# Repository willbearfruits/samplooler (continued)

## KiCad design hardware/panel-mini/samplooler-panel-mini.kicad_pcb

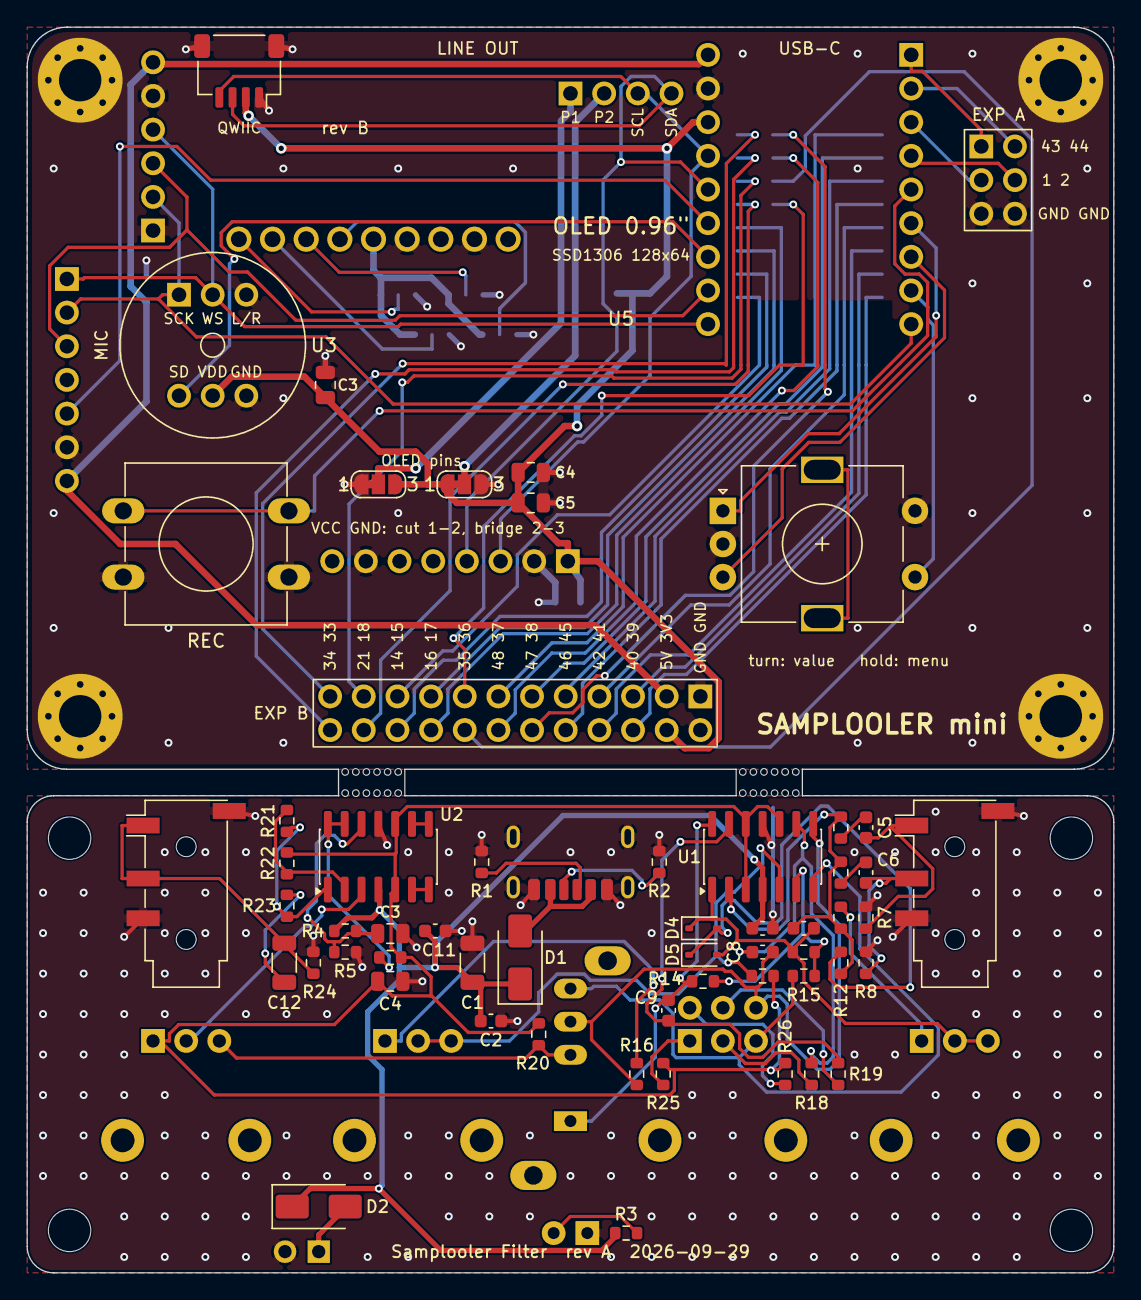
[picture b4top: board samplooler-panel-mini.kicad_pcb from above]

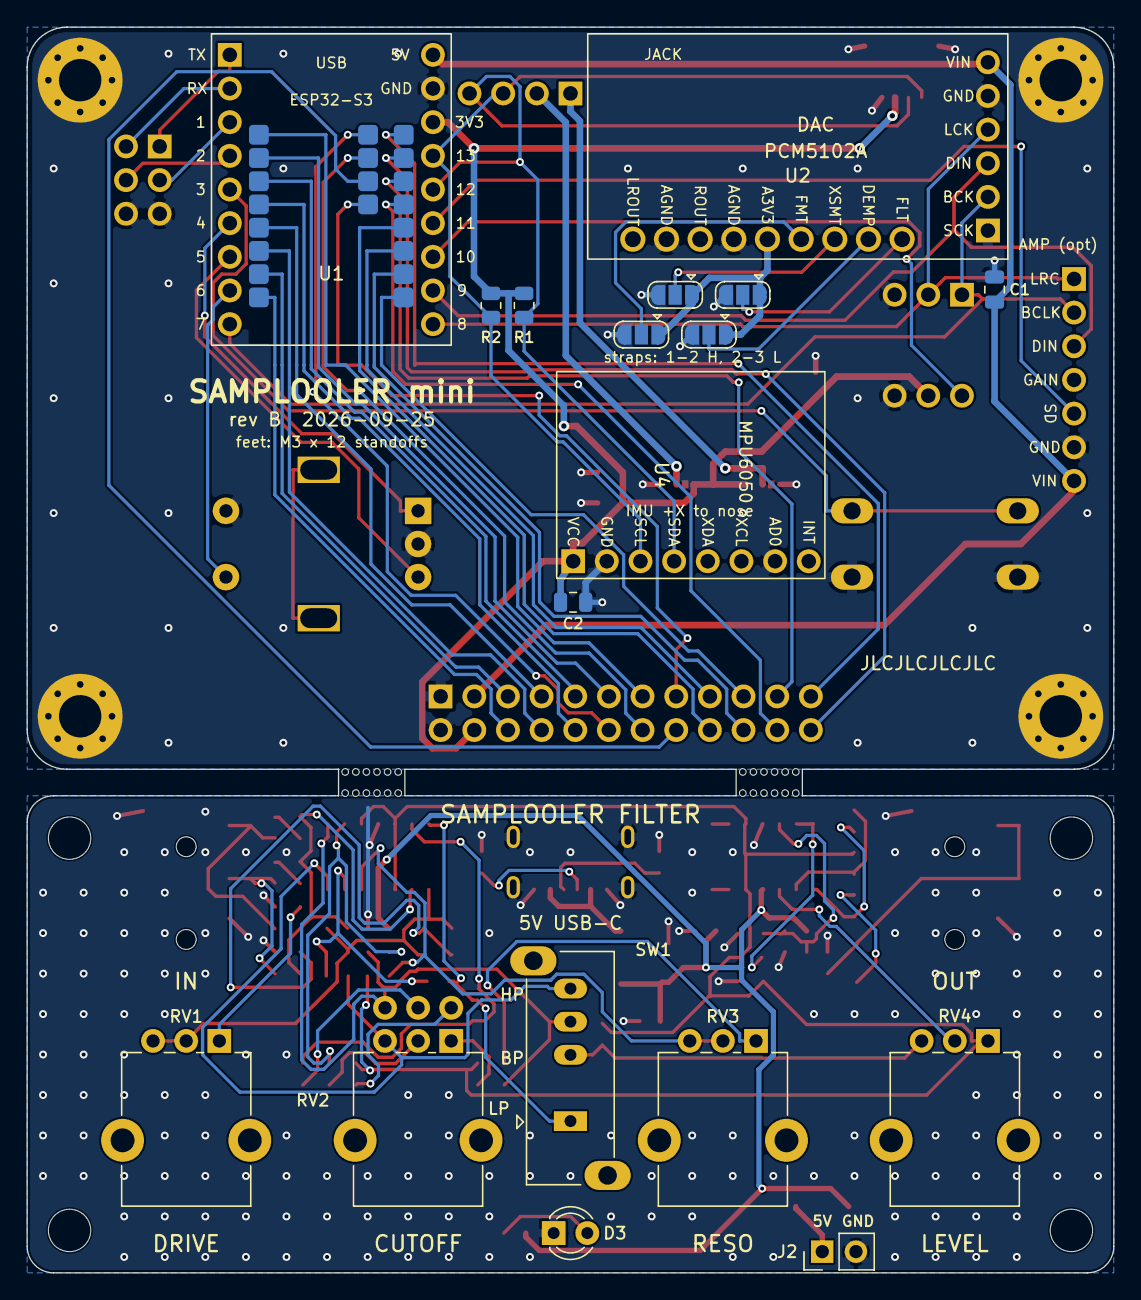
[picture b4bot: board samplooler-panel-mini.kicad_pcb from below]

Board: 2 copper layers, 82.0 x 94.0 mm, 86 parts (19 on the bottom side), 81 nets.

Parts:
C1, C12: 47u; C_1206_3216Metric
C1#2, C3, C4, C4#2: 10u; C_0805_2012Metric
C2, C10, C11: 100n; C_0603_1608Metric
C2#2, C3#2, C5#2: 100n; C_0805_2012Metric
C5, C6: 1u; C_0603_1608Metric
C7: 100p; C_0603_1608Metric
C8, C9: 3.3n; C_0603_1608Metric
D1, D2: SS14; D_SMA
D3: LED 3mm; LED_D3.0mm
D4, D5: 1N4148W; D_SOD-323
H1, H2, H3#2, H4: M3; MountingHole_3.2mm_M3_Pad_Via
H1#2, H2#2, H3, H4#2: M3; MountingHole_3.2mm_M3
J1: USB-C (power); USB_C_Receptacle_HRO_TYPE-C-31-M-17_NoSilkOverPegs
J2: 5V IN; PinHeader_1x02_P2.54mm_Vertical
J2#2: MAX98357A (opt); MAX98357A_Breakout
J3: IN; Jack_3.5mm_PJ320D_Horizontal
J3#2: Qwiic I2C; JST_SH_SM04B-SRSS-TB_1x04-1MP_P1.00mm_Horizontal
J4: OUT; Jack_3.5mm_PJ320D_Horizontal
J4#2: EXP A; EXP_A_2x3_Mini
J5: EXP B; EXP_B_2x12_Mini
JP1: FLT; SolderJumper-3_P1.3mm_Open_RoundedPad1.0x1.5mm
JP2: DEMP; SolderJumper-3_P1.3mm_Open_RoundedPad1.0x1.5mm
JP3: XSMT; SolderJumper-3_P1.3mm_Open_RoundedPad1.0x1.5mm
JP4: FMT; SolderJumper-3_P1.3mm_Open_RoundedPad1.0x1.5mm
JP5: OLED pin 1; SolderJumper-3_P1.3mm_Bridged12_RoundedPad1.0x1.5mm_NumberL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
JP6: OLED pin 2; SolderJumper-3_P1.3mm_Bridged12_RoundedPad1.0x1.5mm_NumberL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
R1, R2: 5k1; R_0603_1608Metric
R1#2, R2#2: 4k7; R_0805_2012Metric
R3, R11, R12: 2k2; R_0603_1608Metric
R4, R5, R14, R15, R22: 10k; R_0603_1608Metric
R6, R25, R26: 100R; R_0603_1608Metric
R7, R8, R20: 100k; R_0603_1608Metric
R9, R10, R21: 22k; R_0603_1608Metric
R13: 33k; R_0603_1608Metric
R16: 470R; R_0603_1608Metric
R17: 1k5; R_0603_1608Metric
R18, R19: 4k7; R_0603_1608Metric
R23: 47R; R_0603_1608Metric
R24: 47k; R_0603_1608Metric
RV1: B100K; Potentiometer_Alpha_RD901F-40-00D_Single_Vertical_CircularH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
RV2: A10K dual; Potentiometer_Alpha_RD902F-40-00D_Dual_Vertical_CircularHol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
RV3: A50K; Potentiometer_Alpha_RD901F-40-00D_Single_Vertical_CircularH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
RV4: A10K; Potentiometer_Alpha_RD901F-40-00D_Single_Vertical_CircularH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
SW1: EC11, 20 mm shaft; RotaryEncoder_Alps_EC11E-Switch_Vertical_H20mm
SW1#2: LP BP HP; SW_Slide_SP3T_Straight_CK_OS103012MU1QP1
SW2: 12 mm tactile + cap; SW_PUSH-12mm
U1, U2: MCP6004; SOIC-14_3.9x8.7mm_P1.27mm
U1#2: ESP32-S3_SuperMini
U2#2: PCM5102A; GY-PCM5102
U3: INMP441; INMP441_Round
U4: MPU6050; GY-521_MPU6050
U5: OLED 0.96in; SSD1306_0.96in_I2C_NoHoles

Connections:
+3V3: C2#2.1, C3#2.1, C4.1, C5#2.1, J3#2.2, J5.4 (3V3), JP5.3, JP6.1, R1#2.1, R2#2.1, U1#2.12 (3V3), U3.5 (VDD), U4.1 (VCC)
+5V: C1.1, C1#2.1, C2.1, C10.1, C11.1, D1.1, D2.1, J2#2.7 (VIN), J5.3 (5V), R3.1, R4.1, U1.4, U1#2.10 (5V), U2.4, U2#2.6 (VIN)
/5V_EXT: D2.2, J2.1
/AC_L: C5.2, R9.1
/AC_R: C6.2, R10.1
/AMP_SD: J2#2.5 (SD), U1#2.15 (11)
/BP: C8.2, R16.1, RV2.6, SW1#2.3, U1.8
/CC1: J1.A5, R1.1
/CC2: J1.B5, R2.1
/CF1: R25.1, RV2.1
/CF2: R26.1, RV2.4
/CLP: D4.2, D5.1, R12.2
/DAC_3V3: JP1.1, JP2.1, JP3.1, JP4.1, U2#2.11 (A3V3)
/DAC_DEMP: JP2.2, U2#2.8 (DEMP)
/DAC_FLT: JP1.2, U2#2.7 (FLT)
/DAC_FMT: JP4.2, U2#2.10 (FMT)
/DAC_XSMT: JP3.2, U2#2.9 (XSMT)
/DRV: C7.2, D4.1, D5.2, R13.1, RV1.2, RV1.3, U1.1
/DRV_N: C7.1, R9.2, R10.2, R11.1, R12.1, U1.2
/DRV_R: R11.2, RV1.1
/ENC_A: SW1.A, U1#2.6 (4)
/ENC_B: SW1.B, U1#2.7 (5)
/ENC_SW: SW1.S1, U1#2.8 (6)
/GPIO1: J4#2.3 (1), U1#2.3 (1)
/GPIO2: J4#2.4 (2), U1#2.4 (2)
/GPIO14: J5.19 (14), U1#2.38 (GPIO14)
/GPIO15: J5.20 (15), U1#2.37 (GPIO15)
/GPIO16: J5.17 (16), U1#2.36 (GPIO16)
/GPIO17: J5.18 (17), U1#2.35 (GPIO17)
/GPIO18: J5.22 (18), U1#2.34 (GPIO18)
/GPIO21: J5.21, U1#2.33 (GPIO21)
/GPIO33: J5.24 (33), U1#2.32 (GPIO33)
/GPIO34: J5.23 (34), U1#2.31 (GPIO34)
/GPIO35: J5.15 (35), U1#2.30 (GPIO35)
/GPIO36: J5.16 (36), U1#2.29 (GPIO36)
/GPIO37: J5.14 (37), U1#2.28 (GPIO37)
/GPIO38: J5.12 (38), U1#2.27 (GPIO38)
/GPIO39: J5.6 (39), U1#2.26 (GPIO39)
/GPIO40: J5.5 (40), U1#2.25 (GPIO40)
/GPIO41: J5.8 (41), U1#2.24 (GPIO41)
/GPIO42: J5.7 (42), U1#2.23 (GPIO42)
/GPIO43: J4#2.1 (43), U1#2.1 (TX)
/GPIO44: J4#2.2 (44), U1#2.2 (RX)
/GPIO45: J5.10 (45), U1#2.22 (GPIO45)
/GPIO46: J5.9 (46), U1#2.21 (GPIO46)
/GPIO47: J5.11 (47), U1#2.20 (GPIO47)
/GPIO48: J5.13 (48), U1#2.19 (GPIO48)
/HP: R15.1, RV2.3, SW1#2.4, U1.7
/I1_N: C8.1, R18.2, U1.9
/I1_W: R18.1, RV2.2
/I2C_SCL: J3#2.4, R2#2.2, U1#2.13, U4.3 (SCL), U5.3 (SCL)
/I2C_SDA: J3#2.3, R1#2.2, U1#2.14 (12), U4.4 (SDA), U5.4 (SDA)
/I2S_BCLK: J2#2.2 (BCLK), U1#2.9 (7), U2#2.2 (BCK), U3.1 (SCK)
/I2S_DIN: U1#2.16 (10), U3.4 (SD)
/I2S_DOUT: J2#2.3 (DIN), U1#2.17 (9), U2#2.3 (DIN)
/I2S_WS: J2#2.1 (LRC), U1#2.18 (8), U2#2.4 (LCK), U3.2 (WS)
/I2_N: C9.1, R19.2, U1.13
/I2_W: R19.1, RV2.5
/IN_L: C5.1, J3.T, R7.1
/IN_R: C6.1, J3.R1, R8.1
/LED_A: D3.2, R3.2
/LEV_W: RV4.2, U2.3
/LP: C9.2, R14.1, SW1#2.1, U1.14
/MODE: R20.1, RV4.3, SW1#2.2
/OLED_P1: JP5.2, U5.1
/OLED_P2: JP6.2, U5.2
/OUT: C12.2, J4.R1, J4.T, R24.1
/OUT_A: R21.1, R23.1, U2.1
/OUT_B: C12.1, R23.2
/OUT_N: R21.2, R22.1, U2.2
/Q_A: R16.2, RV3.1
/REC: SW2.1, U1#2.5 (3)
/SPB: U2.6, U2.7
/SPC: U2.8, U2.9
/SUM_N: R13.2, R14.2, R15.2, U1.6
/SUM_P: R17.1, RV3.2, RV3.3, U1.5
/VBUS: D1.2, J1.A9, J1.B9
/VREF: C4#2.1, R6.2, R17.2, R20.2, R22.2, R25.2, R26.2, RV4.1, U1.3, U1.10, U1.12, U2.5, U2.10
/VREF_D: C3.1, R4.2, R5.1, U2.12
/VREF_O: R6.1, U2.13, U2.14
GND: C1.2, C1#2.2, C2.2, C2#2.2, C3.2, C3#2.2, C4.2, C4#2.2, C5#2.2, C10.2, C11.2, D3.1, H1.1, H2.1, H3#2.1, H4.1, J1.A12, J1.B12, J1.SH, J2.2, J2#2.6 (GND), J3.R2, J3.S, J3#2.1, J3#2.MP, J4.R2, J4.S, J4#2.5 (GND), J4#2.6 (GND), J5.1 (GND), J5.2 (GND), JP1.3, JP2.3, JP3.3, JP4.3, JP5.1, JP6.3, R1.2, R2.2, R5.2, R7.2, R8.2, R24.2, SW1.C, SW1.S2, SW2.2, U1.11, U1#2.11 (GND), U2.11, U2#2.1 (SCK), U2#2.5 (GND), U2#2.12 (AGND), U2#2.14 (AGND), U3.3 (L/R), U3.6 (GND), U4.2 (GND), U4.7 (AD0)

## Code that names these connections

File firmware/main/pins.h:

// Pin map, identical to the ESP32-S3 SuperMini kit (~/Projects/kit/docs/pinmap.md).
#pragma once

#define PIN_BOOT      0    // BOOT button, active low
#define PIN_I2S_BCLK  7    // -> INMP441 SCK, PCM5102A BCK
#define PIN_I2S_WS    8    // -> INMP441 WS,  PCM5102A LCK
#define PIN_I2S_DOUT  9    // -> PCM5102A DIN   (PCM5102A: SCK to GND, XSMT bridged H, or it is silent)
#define PIN_I2S_DIN   10   // <- INMP441 SD     (L/R to GND or VDD, both accepted)
#define PIN_I2C_SDA   12   // MPU6050 at 0x68, plus the kit's OLED at 0x3C
#define PIN_I2C_SCL   13
#define OLED_ENABLE   1
#define OLED_W        128  // the kit's 0.96" panel
#define OLED_H        64
#define PIN_AMP_SD    11   // kit speaker amp: driven high so the speaker plays; set -1 to leave it off
#define HAS_CONTROLS  1    // encoder: tap = menu / dive / back, hold = leave the menu, turn = choose or adjust
#define HAS_JOY       0    // 1 on a kit with the KY-023 joystick: Y sets the speed when tilt is off, X the pitch
#define PIN_REC       3    // record button to GND (the Mini board's REC; the joystick's old click pin)
#define PIN_JOY_X     2    // ADC1 (ADC2 dies with WiFi)   (HAS_JOY only)
#define PIN_JOY_Y     1
#define PIN_JOY_SW    3    // active low
#define PIN_ENC_A     4
#define PIN_ENC_B     5
#define PIN_ENC_SW    6    // active low: menu
#define ENC_STEPS     4    // counts per detent
#define ENC_DIR      -1    // the stack board's encoder counts the other way round from the kit's
